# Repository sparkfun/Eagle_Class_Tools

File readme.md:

Note: to delete previous settings delete "Cadsoft" folder in "C:\Users\jim.lindblom\AppData\Roaming"

### Download and Install Eagle

Link: [http://www.cadsoftusa.com/download-eagle/?language=en](http://www.cadsoftusa.com/download-eagle/?language=en)

File Name: eagle-win-6.4.0.exe (Windows), eagle-mac-6.4.0.zip (Mac)

1. Run WinZip Self-Extractor.
2. Setup (Wait about a minute).
3. Next on Welcome Screen.
4. Yes to license agreement.
5. Decide destination directory, Click Next
6. Click next to start copying files. Wait a minute.
7. Select "Run as Freeware". Click Next.
	* Freeware limitations? !!! TODO
8. Click Finish.

### Run Eagle for First Time

Click "Yes" to any/all directory creations

### Setting Up the Control Panel

1. Overview about each tree.
	* Click on an example in each tree, and show how information panel changes.
	* Explain green dots.
2. Show "Directories" Dialog
	* Options > Directories
	* Point Libraries to our library folder (.../Eagle Class Files/lbrClass). In addition to current directory.
	* Point Scripts to our folder (.../Eagle Class Files/scrClass). In addition to current directory.
	* Show how lbrClass and scrClass directories are added to tree view.
3. Set Libraries to USE NONE from default folder. Make sure lbrClass folder is used.
	* Explain why we won't be using default libraries. Too overwhelming.
	* Right-click **Libraries** tree, click **Use None**.
	* Should make all green dots go away.
	* Talk a bit more about library. Expand and look at parts. This is a good place to explain symbiosis between board and package.
4. Create a New Project
	* Right click "eagle" folder. Select **New Project**. Title folder "Bare Bones Arduino".
	* Explain difference between regular folder, and project folder.
	* Explain green dot again.
5. Create a Schematic in Project
	* Right click project folder. Select **New > Schematic**.
	* Schematic editor should open

### Schematic: Add tool. Moving around the frame. Adding a frame.

1. Explain the Schematic Editor View
	* Explain **toolbar**. We'll talk more in-depth about each tool as we encounter it.
	* Every tool can also be accessed from Draw, View, Tools menu.
2. Add a frame.
	* Click "Add" button (looks like And gate, with black arrow over it). Also found under **Edit** menu.
	* Explain what add tool does.
	* Should only be one library -- spk1 -- in add view. **Ask if people see more/not spk1.**
	* Expand spk1. Select **FRAME-LETTER**. Either double-click it, or select and click OK.
	* Frame will "Glow" and follow mouse around. Move mouse over dotted cross (origin) and **LEFT CLICK** to place the frame. 
	* Another frame will follow mouse around. We don't want to place another, so **Hit ESC**.
	* Hit ESC again to get out of add view
3. Explain grid/origin
	* Set the grid with "Grid" tool (icon under open). Also under View menu.
	* Show where mouse coordinates are displayed.
4. Explain how to navigate with mouse around schematic.
	* Middle mouse button zooms in/out
	* Hold middle mouse down, and drag mouse to move around screen.
	* If student doesn't have a mouse, view tools become useful. Show where zoom in/out, zoom to fit, and zoom select are.
5. Save schematic -- file name bareBonesArduino.sch
	* After saving, you can hit "Redraw". The title will be added to the frame. Date wil be updated.

### Add Power Input Circuitry. Making the first wires. Moving parts.

1. Add POWER_JACKPTH
	* Explain why different footprints for jack.
	* Add to top left of frame.
	* Hit ESC, ESC to get out
	* Explain value and name parameters.
2. Add Capacitor
	* CAP > CAPPTH
	* Place near the jack. ESC, ESC
3. Add two Ground Nodes
	* One below jack. One below cap.
4. Add one VCC node
	* Above cap.
5. Net VCC
	* Explain why use "Net" tool, and not "Wire"
	* Explain how the net tool works.
	* Start at a "Pin" (explain how to recognize pins, different parts have different amounts of pins), and finish at another pin.
	* Wire from barrel Jack + to top of cap.
	* Can also start on net. Always need to finish at a pin (or else hit ESC).
	* Wire from net bend to VCC pin.
	* When connecting more than two pins to a net, a Warning dialog will pop up. Usually, you'll have meant to merge the pins to one net, so click Yes.
	* A node junction should be created when creating a three-way junction.
6. Net GND
	* to pins to route on barrel jack to GND node
	* Route bottom fo cap to GND
7. Explain the MOVE tool
	* Moving a part is a good way to check if nets are connected.

### Create a Board File. Setup environment by running script.

1. Click the "Generate/switch to Board" tool. Under the File menu.
	* If board is being created, it'll ask if you want to. Click Yes.
2. New Board should be created with the parts we've added.
3. Explain the ratsnest wires.
4. Run script file -- spk.scr
	* May need to navigate to script directory (Eagle Class Files/scrClass)
	* This should turn background black. Explain why we like to differentiate. Show how this can be adjusted.
5. Save board. And go back to schematic. 

### Add ATmega328

1. Add: AVR-MEGA8-PPTH
	* Place it in the center of schematic
2. Bring board back up. Show that ATmega was added there as well.
3. Don't close board! Explain why don't close board! Explain green dots.

### Adding resistors. Group Move. Value tool. Rotating parts.

1. Add three resistors (RESISTORAXIAL-0.3)
	* One vertical near reset pin.
	* Three to lower-right portion of sheet
	* ESC ESC
	* Show how names are being auto-incremented. 
	* Add values to resistors. 10k on reset, 220 on LEDs.
	* We also need to go back and **value capacitor**(0.1uF)
2. Add three LEDs (LED5MM)
	* Place them below the resistors
3. Need to group move LEDs.
	* Group LEDs
	* Select Move tool
	* Point out status bar text directions.
	* Hold ctrl+right click to move group.
	* Move group of LEDs on top of resistor.
4. Add a capacitor (CAPPTH)
	* We want cap to go horizontally.
	* Right click once to rotate cap 90&deg;.
	* Can also use rotation (quadrant) tools top left.
	* Place cap to left/bottom of reset resistor. Pins even with reset pin.
	* Value cap at 0.1uF
5. Add 6-pin connector (FTDI_BASICPTH)
	* Place in bottom left
6. Add 8-pin connector (M081X08)
	* **Flip the part** by middle clicking.
	* Place in top-right of frame.
7. Add AVR programmer (AVR_SPI_PRG_6PTH)
	* Place below AVR
8. Add 5 GNDs
	* One for AVR
	* One for ISP
	* Three for LEDs
9. Add 3 VCCs
	* One for AVR
	* One for reset pull-up
	* One for ISP

### Wire up the remaining parts -- Naming nets

1. Reinforce using NET tool!
2. Start on LEDs. Same as before. Go from AVR to LED (PB0, PB1, PB2). LED to resistor. resistor to GND.\
3. Wire up VCC and GND on AVR
	* Make sure nodes appear!
3. Wire up reset circuit
	* Resest pin to resistor and capacitor
	* Resistor pulled up to 3.3V
	* Wire to nowhere (about three grid spaces) on other end of cap.
4. Name your first net
	* Name net DTR
	* Use label tool to add name to net.
5. Wire up serial header.
	* Make six nets. Name all accordingly. Label each net.
	* Can label before naming.
	* Nets that are already named will ask if you want to make the connection. Good sign. Click yes.
6. Label RX and TX on AVR 
	* Use **Show tool** to show that pins are connected.
7. Wire up ISP connector
8. Make MISO, MOSI, SCK, RESET nets on AVR
9. Add connections to A0-A5 and VCC, GND on 8-pin header
10. Make same (analog) connections on AVR.

TA DA!

### Arrange parts on board. Fit dimensions layer.

1. Switch to board editor
	* DON'T CLOSE SCHEMATIC!
2. All parts should have been added to editor as well.
3. Explain visible layers: dimensions, via, tsilk, tdoc, ratsnest.
4. Move ATmega328 to middle of board.
	* Have to click part origin to move it.
	* Use right click to rotate
	* Note on how airwires remain attached.
5. Arranging parts is all about making our routing easier. Try to criss-cross airwires as rarely as possible.
6. Move 8-pin analog header to right of IC.'
	* Show how much more difficult it'll be if rotated incorrectly.
7. More LEDs, arrange resistors nearby.
	* Explain why the green dots can't overlap (it's copper!)
8. Place ISP header.
	* Overlaps are inevitable.
9. Place serial 6-pin header.
10. Move DTR cap near serial header.
11. Move pull-up resistor between DTR and reset pin.
12. Add barrel jack and decoupling cap to top left of board.
	* Explain barrel jack's tDoc layer.
13. Adjust dimension layer lines to better fit our board.
14. Can group move entire board to align bottom left with origin.
15. Contest to have smallest, routed board?

### Start Routing

1. Explain top and bottom layers.

### Auto-router

###

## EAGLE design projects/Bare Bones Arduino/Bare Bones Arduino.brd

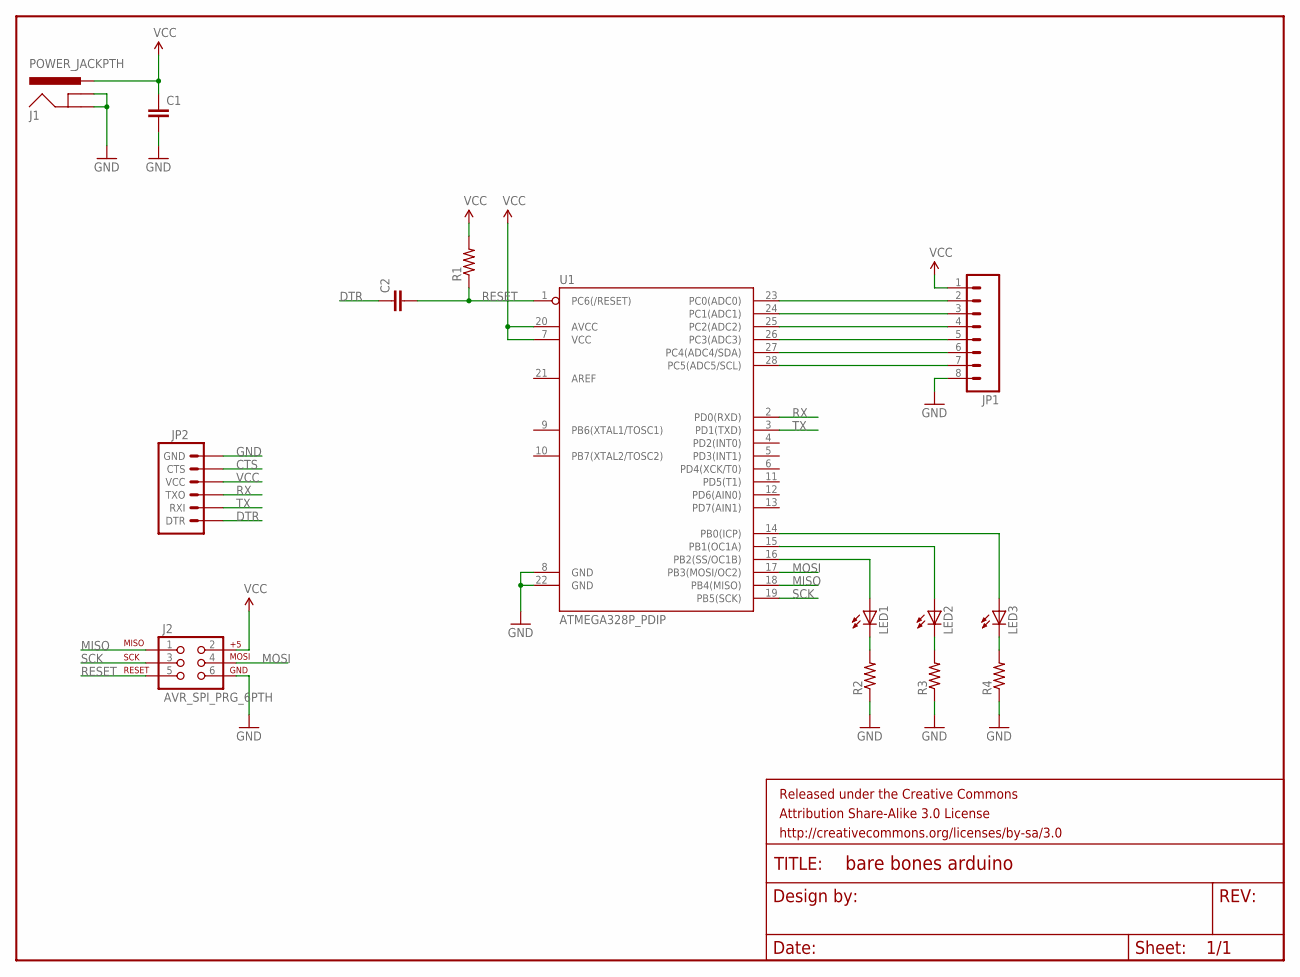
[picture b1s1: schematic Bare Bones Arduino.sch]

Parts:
C1, C2: CAPPTH; CAP-PTH-SMALL
FRAME1: FRAME-LETTER; CREATIVE_COMMONS
J1: POWER_JACKPTH; POWER_JACK_PTH
J2: AVR_SPI_PRG_6PTH; 2X3
JP1: M081X08; 1X08
JP2: ARDUINO_SERIAL_PROGRAMPTH; 1X06
LED1, LED2, LED3: LED5MM
R1, R2, R3, R4: RESISTORPTH-1/4W; AXIAL-0.4
U1: ATMEGA328P_PDIP; DIL28-3

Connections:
CTS: JP2.5 (CTS)
DTR: C2.1, JP2.1 (DTR)
GND: C1.2, J1.GND, J1.GNDBREAK, J2.6, JP1.8, JP2.6 (GND), R2.P$1 (1), R3.P$1 (1), R4.P$1 (1), U1.8 (GND), U1.22 (GND)
MISO: J2.1, U1.18 (PB4(MISO))
MOSI: J2.4, U1.17 (PB3(MOSI/OC2))
unnamed: LED1.A, U1.16 (PB2(SS/OC1B))
unnamed: LED2.A, U1.15 (PB1(OC1A))
unnamed: LED3.A, U1.14 (PB0(ICP))
unnamed: LED1.K (C), R2.P$2 (2)
unnamed: LED2.K (C), R3.P$2 (2)
unnamed: LED3.K (C), R4.P$2 (2)
unnamed: JP1.2, U1.23 (PC0(ADC0))
unnamed: JP1.3, U1.24 (PC1(ADC1))
unnamed: JP1.4, U1.25 (PC2(ADC2))
unnamed: JP1.5, U1.26 (PC3(ADC3))
unnamed: JP1.6, U1.27 (PC4(ADC4/SDA))
unnamed: JP1.7, U1.28 (PC5(ADC5/SCL))
RESET: C2.2, J2.5, R1.P$1 (1), U1.1 (PC6(/RESET))
RX: JP2.3 (TXO), U1.2 (PD0(RXD))
SCK: J2.3, U1.19 (PB5(SCK))
TX: JP2.2 (RXI), U1.3 (PD1(TXD))
VCC: C1.1, J1.PWR, J2.2, JP1.1, JP2.4 (VCC), R1.P$2 (2), U1.7 (VCC), U1.20 (AVCC)

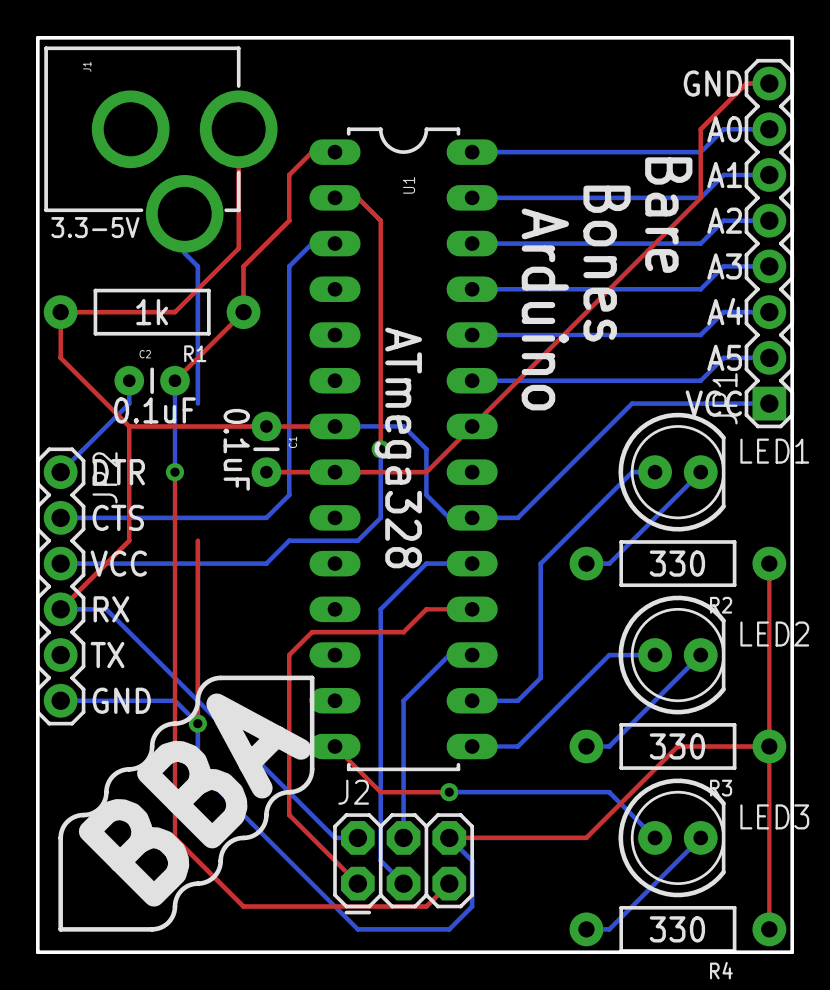
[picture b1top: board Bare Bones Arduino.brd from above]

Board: 2 copper layers, 41.9 x 50.8 mm, 15 parts (0 on the bottom side), 21 nets.

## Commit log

2013-07-24 initial commit of cam, dru, lbr, project, script
2013-07-24 Adding Readme (work in progress)
2013-08-16 Updating Eagle files, adding documentation
2013-08-16 Updating library
2013-08-16 Renaming documentation files. Adding HTML versions.
2025-06-27 Update 01_SettingUpEagle.md
    Updating links
2025-06-27 Update 02_UsingEAGLESchematic.md
    Updating links
2025-06-27 Update 01_SettingUpEagle.html
    Updating links
2025-06-27 Update 03_UsingEAGLEBoardLayout.md
    Updating links
2025-06-27 Update 02_UsingEAGLESchematic.html
    Updating links
2025-06-27 Update 03_UsingEAGLEBoardLayout.html
    Updating links

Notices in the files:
parts and their libraries:
SparkFun-Aesthetics: Licensing: CC v3.0 Share-Alike You are welcome to use this library for commercial purposes.
SparkFun-Aesthetics: Released under the Creative Commons Attribution Share-Alike 3.0 License
SparkFun-Aesthetics: http://creativecommons.org/licenses/by-sa/3.0
